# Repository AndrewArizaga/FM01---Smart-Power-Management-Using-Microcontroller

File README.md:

# FM01: Smart Power Management Using Microcontroller

## Overview
The **Smart Power Management Using Microcontroller** project is a practical solution designed to automate the switching of lights and appliances based on room occupancy and individual iris recognition. Leveraging the ESP32 microcontroller, this project aims to provide energy efficiency, ease of use, and enhanced security.

---

## Key Objectives
- **Energy Efficiency:** Automatically turn off unused appliances and lights to conserve energy.
- **Convenience:** Enable seamless automation for modern smart homes.
- **Enhanced Security:** Incorporate iris recognition for selective activation.

---

## Hardware Components
- **ESP32-WROOM-32D:** Core microcontroller for processing and control.
- **IR Sensors:** Detect room occupancy.
- **Relay Modules:** Control high-power devices such as lights and appliances.
- **Iris Recognition Module:** Authenticate user identity.
- **Power Supply:** Provides power for the microcontroller and connected peripherals.
- **Push Buttons:** For manual override and system programming.

---

## System Workflow
1. **Occupancy Detection:**
   - IR sensors detect room occupancy and send signals to the ESP32.
2. **Iris Recognition:**
   - The iris recognition module authenticates the user.
3. **Appliance Control:**
   - Upon successful detection and authentication, the ESP32 activates relays to power appliances and lights.
4. **Energy Optimization:**
   - When the room is unoccupied, the system automatically turns off the connected devices.

---

## Project Focus
This project emphasizes:
- **Practical Implementation:** Integrating automation with embedded systems for smart homes.
- **Energy Conservation:** Reducing energy waste through smart automation.
- **User Security:** Ensuring only authorized users can access specific features.

---

## Future Applications
- **Smart Homes:** Enhance home automation with personalized settings and energy tracking.
- **Industrial Automation:** Implement efficient power management systems in factories and offices.
- **IoT Ecosystems:** Integrate with IoT platforms for real-time monitoring and control.

---

## How to Use
1. Power the system using a suitable power supply.
2. Approach the room to trigger the **occupancy detection** system.
3. Authenticate your identity using the **iris recognition module**.
4. The system will automatically switch on the connected appliances.
5. When leaving the room, ensure no occupancy to enable the **auto-off** feature.

---

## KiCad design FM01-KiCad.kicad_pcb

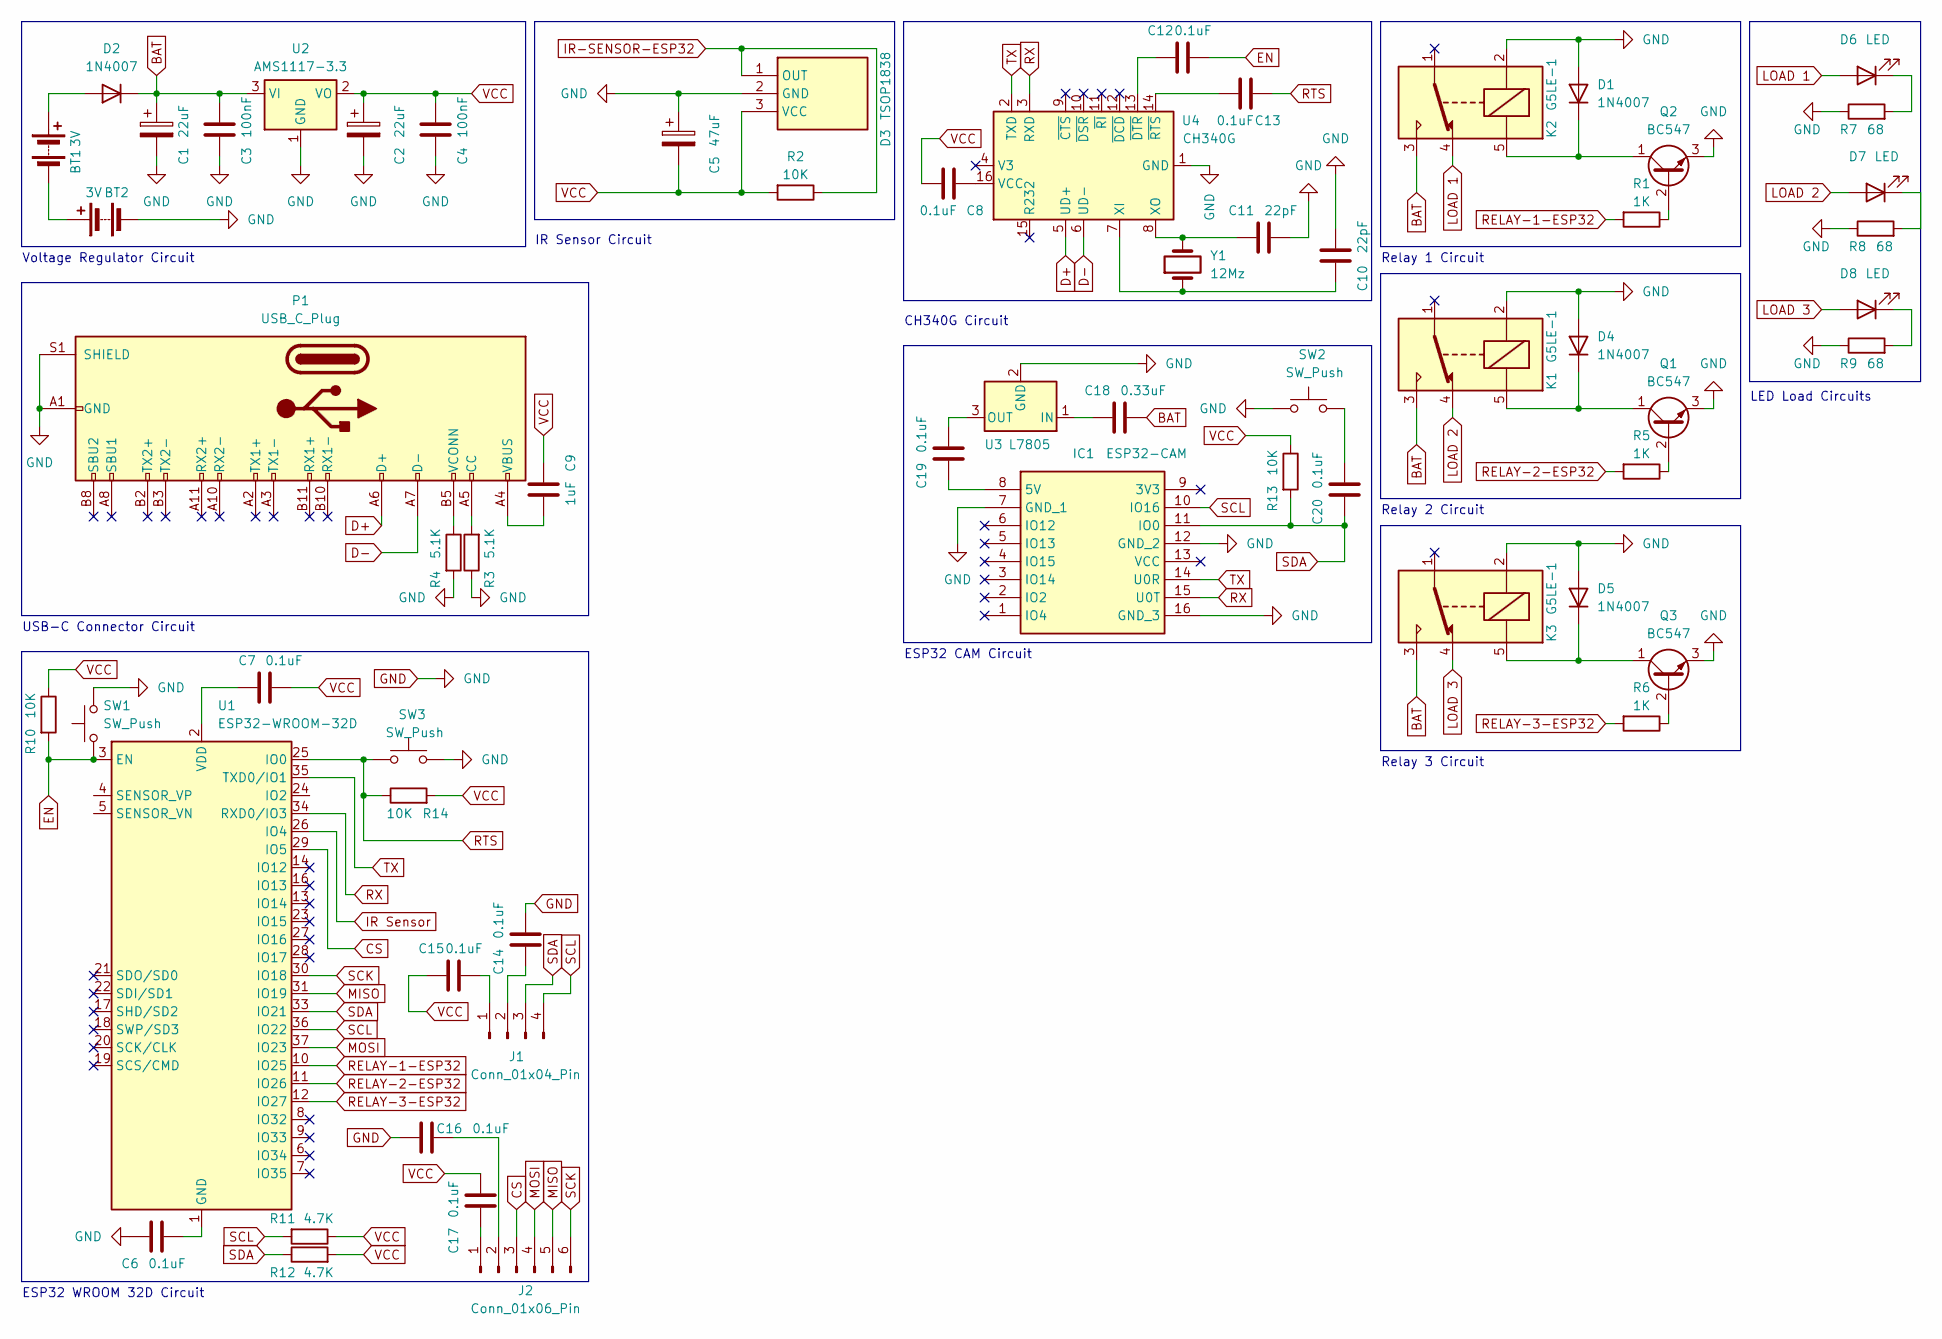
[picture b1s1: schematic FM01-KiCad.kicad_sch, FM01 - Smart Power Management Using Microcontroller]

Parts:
BT1, BT2: 3V; BatteryHolder_Keystone_2468_2xAAA
C1, C2: 22uF; C_1206_3216Metric_Pad1.33x1.80mm_HandSolder
C3, C4: 100nF; C_0805_2012Metric_Pad1.18x1.45mm_HandSolder
C5: 47uF; C_1206_3216Metric_Pad1.33x1.80mm_HandSolder
C6, C7, C8, C12, C13, C14, C15, C16, C17, C19, C20: 0.1uF; C_0805_2012Metric_Pad1.18x1.45mm_HandSolder
C9: 1uF; C_0805_2012Metric_Pad1.18x1.45mm_HandSolder
C10, C11: 22pF; C_0805_2012Metric_Pad1.18x1.45mm_HandSolder
C18: 0.33uF; C_0805_2012Metric_Pad1.18x1.45mm_HandSolder
D1, D2, D4, D5: 1N4007; D_DO-41_SOD81_P10.16mm_Horizontal
D3: TSOP1838; TSOP4856; Manufacturer_Part_Number TSOP1838; Mouser Part Number 78-TSOP1838
D6, D7, D8: LED; LED_D3.0mm
IC1: ESP32-CAM; ESP32CAM; Manufacturer_Part_Number ESP32-CAM
J1: Conn_01x04_Pin; PinHeader_1x04_P2.54mm_Vertical
J2: Conn_01x06_Pin; PinHeader_1x06_P2.54mm_Vertical
K1, K2, K3: G5LE-1; Relay_SPDT_Omron-G5LE-1
P1: USB_C_Plug; USB_C_Receptacle_Molex_105450-0101
Q1, Q2, Q3: BC547; TO-92_Inline
R1, R5, R6: 1K; R_0805_2012Metric_Pad1.20x1.40mm_HandSolder
R2, R10, R13, R14: 10K; R_0805_2012Metric_Pad1.20x1.40mm_HandSolder
R3, R4: 5.1K; R_0805_2012Metric_Pad1.20x1.40mm_HandSolder
R7, R8, R9: 68; R_0805_2012Metric_Pad1.20x1.40mm_HandSolder
R11, R12: 4.7K; R_0805_2012Metric_Pad1.20x1.40mm_HandSolder
SW1, SW2, SW3: SW_Push; SW_Push_1P1T_NO_6x6mm_H9.5mm
U1: ESP32-WROOM-32D
U2: AMS1117-3.3; SOT-223-3_TabPin2
U3: L7805; TO-220-3_Vertical
U4: CH340G; SOIC-16_3.9x9.9mm_P1.27mm
Y1: 12Mz; Crystal_HC49-U_Vertical

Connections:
BAT: C1.1, C3.1, C18.1, D2.1 (K), K1.3, K2.3, K3.3, U2.3 (VI)
CS: J2.3, U1.29 (IO5)
D+: P1.A6 (D+), U4.5 (UD+)
D-: P1.A7 (D-), U4.6 (UD-)
EN: C12.1, R10.2, SW1.1, U1.3 (EN)
GND: BT2.2 (-), C1.2, C2.2, C3.2, C4.2, C5.1, C6.2, C10.2, C11.1, C14.1, C16.2, D1.2 (A), D3.2 (GND), D4.2 (A), D5.2 (A), IC1.7 (GND_1), IC1.12 (GND_2), IC1.16 (GND_3), K1.2, K2.2, K3.2, P1.A1 (GND), P1.A12 (GND), P1.B1 (GND), P1.B12 (GND), P1.S1 (SHIELD), Q1.3 (E), Q2.3 (E), Q3.3 (E), R3.1, R4.2, R7.1, R8.1, R9.1, SW1.2, SW2.1, SW3.2, U2.1 (GND), U3.2 (GND), U4.1 (GND)
IR Sensor: U1.26 (IO4)
IR-SENSOR-ESP32: D3.1 (OUT), R2.1
LOAD 1: D6.2 (A), K2.4
LOAD 2: D7.2 (A), K1.4
LOAD 3: D8.2 (A), K3.4
MISO: J2.5, U1.31 (IO19)
MOSI: J2.4, U1.37 (IO23)
unnamed: BT1.1 (+), D2.2 (A)
unnamed: BT1.2 (-), BT2.1 (+)
unnamed: C6.1, U1.1 (GND), U1.15 (GND), U1.38 (GND), U1.39 (GND)
unnamed: C9.1, P1.A4 (VBUS), P1.A9 (VBUS), P1.B4 (VBUS), P1.B9 (VBUS)
unnamed: C20.1, SW2.2
unnamed: D1.1 (K), K2.5, Q2.1 (C)
unnamed: D4.1 (K), K1.5, Q1.1 (C)
unnamed: D5.1 (K), K3.5, Q3.1 (C)
unnamed: D6.1 (K), R7.2
unnamed: D7.1 (K), R8.2
unnamed: D8.1 (K), R9.2
unnamed: C19.2, IC1.8 (5V)
unnamed: C15.1, J1.1
unnamed: C14.2, J1.2
unnamed: C17.2, J2.1
unnamed: C16.1, J2.2
unnamed: P1.A5 (CC), R3.2
unnamed: P1.B5 (VCONN), R4.1
unnamed: Q1.2 (B), R5.1
unnamed: Q2.2 (B), R1.1
unnamed: Q3.2 (B), R6.1
unnamed: C7.2, U1.2 (VDD)
unnamed: C18.2, U3.1 (IN)
unnamed: C19.1, U3.3 (OUT)
unnamed: C8.2, U4.16 (VCC)
unnamed: C10.1, U4.7 (XI), Y1.1
unnamed: C11.2, U4.8 (XO), Y1.2
unnamed: C12.2, U4.13 (~DTR)
unnamed: C13.1, U4.14 (~RTS)
RELAY-1-ESP32: R1.2, U1.10 (IO25)
RELAY-2-ESP32: R5.2, U1.11 (IO26)
RELAY-3-ESP32: R6.2, U1.12 (IO27)
RTS: C13.2, R14.1, SW3.1, U1.25 (IO0)
RX: IC1.15 (U0T), U1.34 (RXD0/IO3), U4.3 (RXD)
SCK: J2.6, U1.30 (IO18)
SCL: IC1.10 (IO16), J1.4, R11.2, U1.36 (IO22)
SDA: C20.2, IC1.11 (IO0), J1.3, R12.1, R13.2, U1.33 (IO21)
TX: IC1.14 (U0R), U1.35 (TXD0/IO1), U4.2 (TXD)
VCC: C2.1, C4.1, C5.2, C7.1, C8.1, C9.2, C15.2, C17.1, D3.3 (VCC), R2.2, R10.1, R11.1, R12.2, R13.1, R14.2, U2.2 (VO)

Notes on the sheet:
LED Load Circuits
Relay 2 Circuit
Relay 1 Circuit
Relay 3 Circuit
IR Sensor Circuit
ESP32 WROOM 32D Circuit
USB-C Connector Circuit
Voltage Regulator Circuit
ESP32 CAM Circuit
CH340G Circuit

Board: 2 copper layers, 62 parts (0 on the bottom side), 51 nets, no tracks yet.

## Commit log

2024-12-27 Initial commit for FM01 project
2024-12-27 Rename FM01-KiCad.kicad_pcb to KiCAD/FM01-KiCad.kicad_pcb
2024-12-27 Rename FM01-KiCad.kicad_prl to KiCAD/FM01-KiCad.kicad_prl
2024-12-27 Rename FM01-KiCad.kicad_pro to KiCAD/FM01-KiCad.kicad_pro
2024-12-27 Rename FM01-KiCad.kicad_sch to KiCAD/FM01-KiCad.kicad_sch
2024-12-27 Rename fp-info-cache to KiCAD/fp-info-cache
2024-12-27 Rename fp-lib-table to KiCAD/fp-lib-table
2024-12-27 Rename report.txt to KiCAD/report.txt
2024-12-27 Rename sym-lib-table to KiCAD/sym-lib-table
2024-12-28 Rename FM01-KiCad.pdf to PDFs&Images/FM01-KiCad-Schematic.pdf
2024-12-28 Rename FM01-KiCad-Schematic.pdf to FM01-KiCad-Schematic-Ver-1.pdf
